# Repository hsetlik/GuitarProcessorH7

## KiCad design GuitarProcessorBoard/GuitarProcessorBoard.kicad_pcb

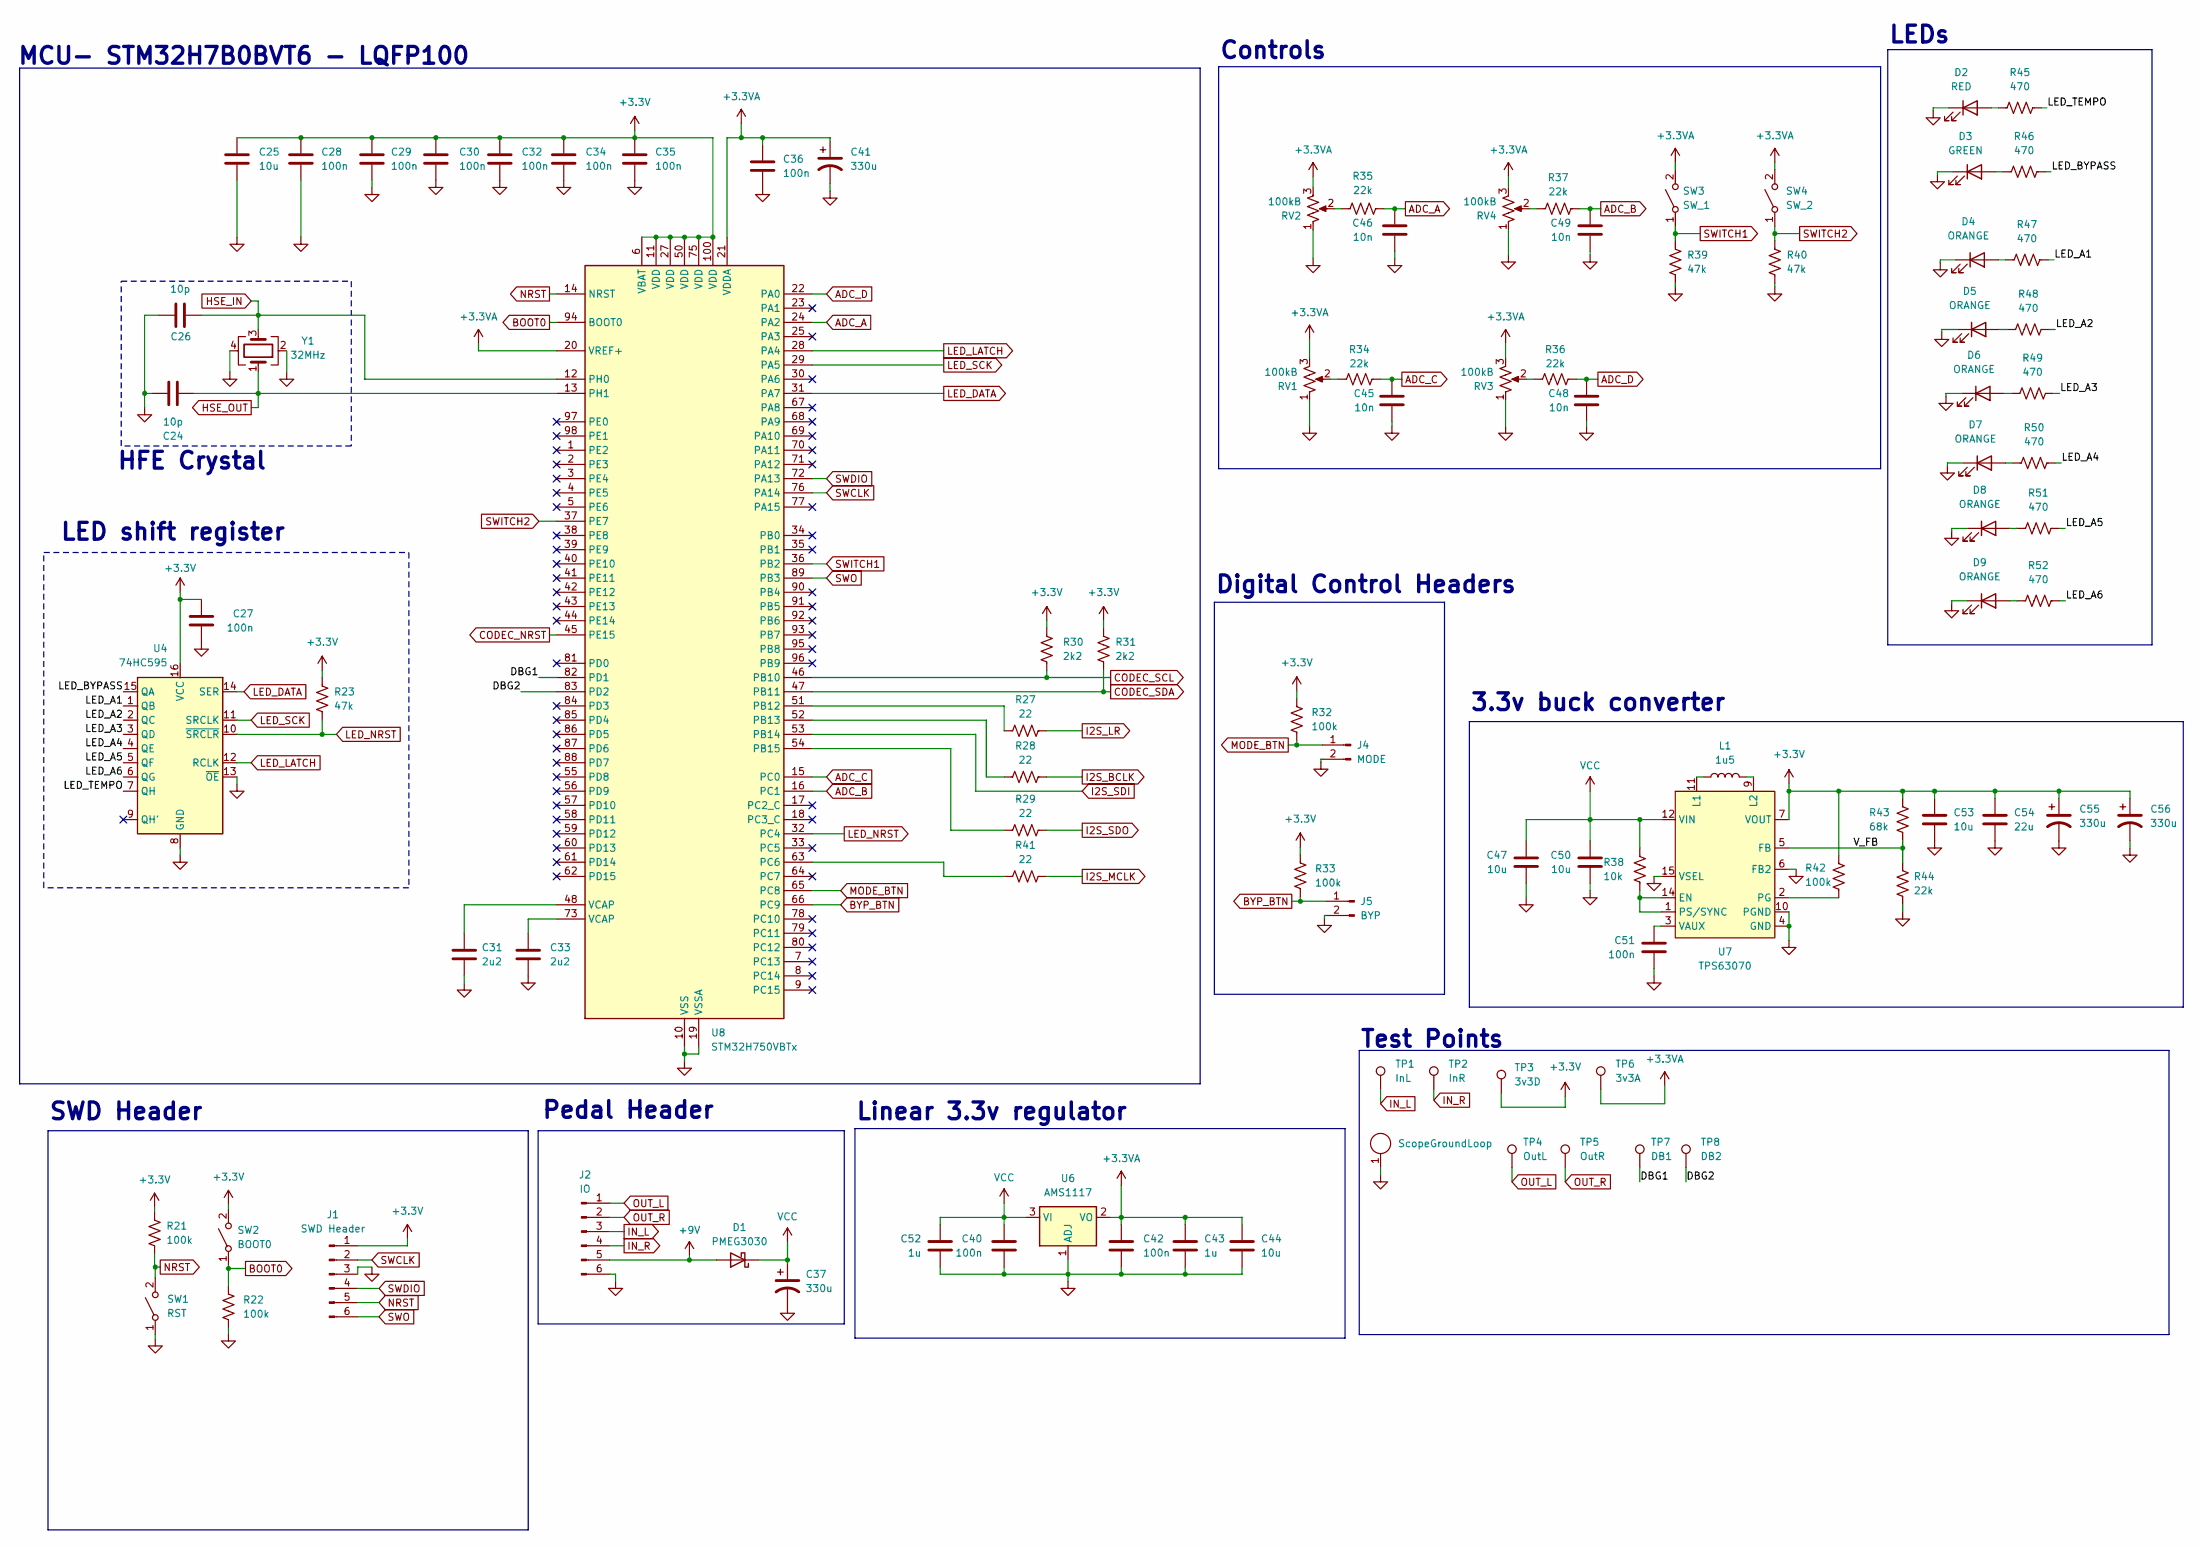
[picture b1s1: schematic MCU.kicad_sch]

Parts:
C24, C26: 10p; C_0805_2012Metric
C25, C44, C47, C50, C53: 10u; C_0805_2012Metric
C27, C28, C29, C30, C32, C34, C35, C36, C40, C42, C51: 100n; C_0805_2012Metric
C31, C33: 2u2; C_0805_2012Metric
C37, C41, C55, C56: 330u; CP_Radial_D5.0mm_P2.50mm
C43, C52: 1u; C_0805_2012Metric
C45, C46, C48, C49: 10n; C_0805_2012Metric
C54: 22u; C_0805_2012Metric
D1: PMEG3030; D_SOD-123
D2: RED; LED_D3.0mm
D3: GREEN; LED_D3.0mm
D4, D5, D6, D7, D8, D9: ORANGE; LED_D3.0mm
J1: SWD Header; PinHeader_1x06_P2.54mm_Vertical
J2: IO; PinHeader_1x06_P2.54mm_Vertical
J3: ScopeGroundLoop; THT_GND_WIRE
J4: MODE; PinHeader_1x02_P2.54mm_Vertical
J5: BYP; PinHeader_1x02_P2.54mm_Vertical
L1: 1u5; L_Coilcraft_XAL4020-XXX
R21, R22, R32, R33, R42: 100k; R_0805_2012Metric
R23, R39, R40: 47k; R_0805_2012Metric
R27, R28, R29, R41: 22; R_0805_2012Metric
R30, R31: 2k2; R_0805_2012Metric
R34, R35, R36, R37, R44: 22k; R_0805_2012Metric
R38: 10k; R_0805_2012Metric
R43: 68k; R_0805_2012Metric
R45, R46, R47, R48, R49, R50, R51, R52: 470; R_0805_2012Metric
RV1, RV2, RV3, RV4: 100kB; Potentiometer_Alpha_RD901F-40-00D_Single_Vertical_CircularH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
SW1: RST; SW_SPST_B3U-1000P
SW2: BOOT0; SW_SPST_B3U-1000P
SW3: SW_1; SW_TH_Tactile_Omron_B3F-102x
SW4: SW_2; SW_TH_Tactile_Omron_B3F-102x
TP1: InL; TestPoint_THTPad_D2.0mm_Drill1.0mm_VAL
TP2: InR; TestPoint_THTPad_D2.0mm_Drill1.0mm_VAL
TP3: 3v3D; TestPoint_THTPad_D2.0mm_Drill1.0mm_VAL
TP4: OutL; TestPoint_THTPad_D2.0mm_Drill1.0mm_VAL
TP5: OutR; TestPoint_THTPad_D2.0mm_Drill1.0mm_VAL
TP6: 3v3A; TestPoint_THTPad_D2.0mm_Drill1.0mm_VAL
TP7: DB1; TestPoint_THTPad_D2.0mm_Drill1.0mm_VAL
TP8: DB2; TestPoint_THTPad_D2.0mm_Drill1.0mm_VAL
U4: 74HC595; SOIC-16_3.9x9.9mm_P1.27mm
U6: AMS1117; SOT-223-3_TabPin2
U7: TPS63070; Converter_DCDC_TXN_QFN15
U8: STM32H750VBTx; LQFP-100_14x14mm_P0.5mm
Y1: 32MHz; Crystal_SMD_EuroQuartz_MT-4Pin_3.2x2.5mm

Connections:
+3.3V: C25.1, C27.1, C28.1, C29.1, C30.1, C32.1, C34.1, C35.1, C53.1, C54.1, C55.1, C56.1, J1.1, R21.1, R23.1, R30.1, R31.1, R32.1, R33.1, R42.1, R43.1, SW2.2 (B), TP3.1 (1_1), U4.16 (VCC), U7.7 (VOUT), U7.8 (VOUT), U8.6 (VBAT), U8.11 (VDD), U8.27 (VDD), U8.50 (VDD), U8.75 (VDD), U8.100 (VDD)
+3.3VA: C36.1, C41.1, C42.2, C43.1, C44.1, RV1.3, RV2.3, RV3.3, RV4.3, SW3.2 (B), SW4.2 (B), TP6.1 (1_1), U6.2 (VO), U8.20 (VREF+), U8.21 (VDDA); also elsewhere on the board
+9V: D1.2 (A), J2.5
/MCU/DBG1: TP7.1 (1_1), U8.82 (PD1)
/MCU/DBG2: TP8.1 (1_1), U8.83 (PD2)
/MCU/LED_A1: R47.2, U4.1 (QB)
/MCU/LED_A2: R48.2, U4.2 (QC)
/MCU/LED_A3: R49.2, U4.3 (QD)
/MCU/LED_A4: R50.2, U4.4 (QE)
/MCU/LED_A5: R51.2, U4.5 (QF)
/MCU/LED_A6: R52.2, U4.6 (QG)
/MCU/LED_BYPASS: R46.2, U4.15 (QA)
/MCU/LED_TEMPO: R45.2, U4.7 (QH)
/MCU/V_FB: R43.2, R44.1, U7.5 (FB)
ADC_A: C46.1, R35.2, U8.24 (PA2)
ADC_B: C49.1, R37.2, U8.16 (PC1)
ADC_C: C45.1, R34.2, U8.15 (PC0)
ADC_D: C48.1, R36.2, U8.22 (PA0)
BOOT0: R22.1, SW2.1 (A), U8.94 (BOOT0)
BYP_BTN: J5.1, R33.2, U8.66 (PC9)
CODEC_NRST: U8.45 (PE15); also elsewhere on the board
CODEC_SCL: R30.2, U8.46 (PB10); also elsewhere on the board
CODEC_SDA: R31.2, U8.47 (PB11); also elsewhere on the board
GND: C24.1, C25.2, C26.1, C27.2, C28.2, C29.2, C30.2, C31.2, C32.2, C33.2, C34.2, C35.2, C36.2, C37.2, C40.1, C41.2, C42.1, C43.2, C44.2, C45.2, C46.2, C47.2, C48.2, C49.2, C50.2, C51.2, C52.2, C53.2, C54.2, C55.2, C56.2, D2.1 (K), D3.1 (K), D4.1 (K), D5.1 (K), D6.1 (K), D7.1 (K), D8.1 (K), D9.1 (K), J1.3, J2.6, J3.1, J4.2, J5.2, R22.2, R39.2, R40.2, R44.2, RV1.1, RV2.1, RV3.1, RV4.1, SW1.1 (A), U4.8 (GND), U4.13 (~OE), U6.1 (ADJ), U7.4 (GND), U7.6 (FB2), U7.10 (PGND), U7.15 (VSEL), U8.10 (VSS), U8.19 (VSSA), U8.26 (VSS), U8.49 (VSS), U8.74 (VSS), U8.99 (VSS), Y1.2, Y1.4; also elsewhere on the board
HSE_IN: C26.2, U8.12 (PH0), Y1.3
HSE_OUT: C24.2, U8.13 (PH1), Y1.1
I2S_BCLK: R28.2; also elsewhere on the board
I2S_LR: R27.2; also elsewhere on the board
I2S_MCLK: R41.2; also elsewhere on the board
I2S_SDI: U8.53 (PB14); also elsewhere on the board
I2S_SDO: R29.2; also elsewhere on the board
IN_L: J2.3, TP1.1 (1_1); also elsewhere on the board
IN_R: J2.4, TP2.1 (1_1); also elsewhere on the board
LED_DATA: U4.14 (SER), U8.31 (PA7)
LED_LATCH: U4.12 (RCLK), U8.28 (PA4)
LED_NRST: R23.2, U4.10 (~SRCLR), U8.32 (PC4)
LED_SCK: U4.11 (SRCLK), U8.29 (PA5)
MODE_BTN: J4.1, R32.2, U8.65 (PC8)
NRST: J1.5, R21.2, SW1.2 (B), U8.14 (NRST)
unnamed: C31.1, U8.48 (VCAP)
unnamed: C33.1, U8.73 (VCAP)
unnamed: D2.2 (A), R45.1
unnamed: D3.2 (A), R46.1
unnamed: D4.2 (A), R47.1
unnamed: D5.2 (A), R48.1
unnamed: D6.2 (A), R49.1
unnamed: D7.2 (A), R50.1
unnamed: D8.2 (A), R51.1
unnamed: D9.2 (A), R52.1
unnamed: R34.1, RV1.2
unnamed: R35.1, RV2.2
unnamed: R36.1, RV3.2
unnamed: R37.1, RV4.2
unnamed: R38.2, U7.1 (PS/SYNC), U7.14 (EN)
unnamed: L1.1, U7.11 (L1)
unnamed: L1.2, U7.9 (L2)
unnamed: R42.2, U7.2 (PG)
unnamed: C51.1, U7.3 (VAUX)
unnamed: R27.1, U8.51 (PB12)
unnamed: R28.1, U8.52 (PB13)
unnamed: R29.1, U8.54 (PB15)
unnamed: R41.1, U8.63 (PC6)
OUT_L: J2.1, TP4.1 (1_1); also elsewhere on the board
OUT_R: J2.2, TP5.1 (1_1); also elsewhere on the board
SWCLK: J1.2, U8.76 (PA14)
SWDIO: J1.4, U8.72 (PA13)
SWITCH1: R39.1, SW3.1 (A), U8.36 (PB2)
SWITCH2: R40.1, SW4.1 (A), U8.37 (PE7)
SWO: J1.6, U8.89 (PB3)
VCC: C37.1, C40.2, C47.1, C50.1, C52.1, D1.1 (K), R38.1, U6.3 (VI), U7.12 (VIN), U7.13 (VIN); also elsewhere on the board

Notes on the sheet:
Pedal Header
3.3v buck converter
Linear 3.3v regulator
LED shift register
Test Points
HFE Crystal
LEDs
MCU- STM32H7B0BVT6 - LQFP100
SWD Header
Controls
Digital Control Headers

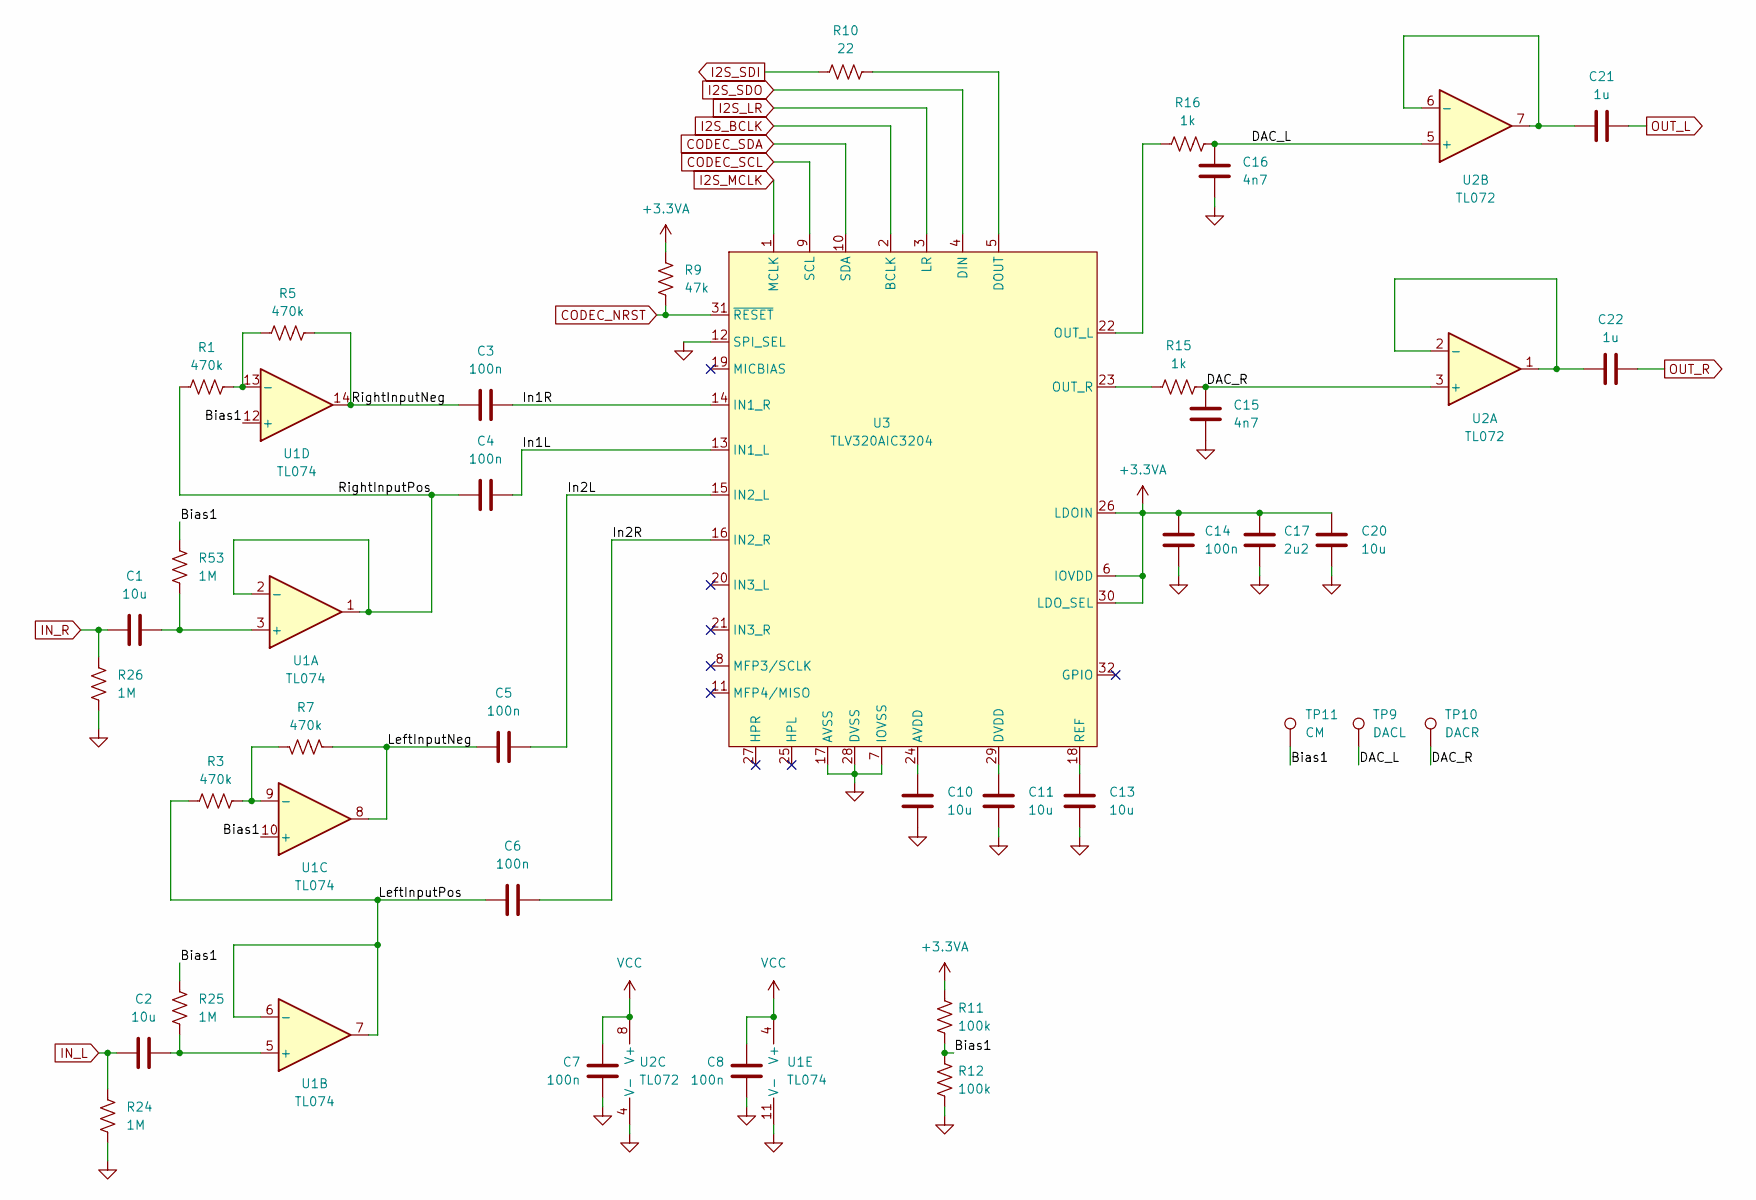
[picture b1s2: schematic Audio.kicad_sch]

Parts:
C1, C2, C10, C11, C13, C20: 10u; C_0805_2012Metric
C3, C4, C5, C6, C7, C8, C14: 100n; C_0805_2012Metric
C15, C16: 4n7; C_0805_2012Metric
C17: 2u2; C_0805_2012Metric
C21, C22: 1u; C_0805_2012Metric
R1, R3, R5, R7: 470k; R_0805_2012Metric
R9: 47k; R_0805_2012Metric
R10: 22; R_0805_2012Metric
R11, R12: 100k; R_0805_2012Metric
R15, R16: 1k; R_0805_2012Metric
R24, R25, R26, R53: 1M; R_0805_2012Metric
TP9: DACL; TestPoint_THTPad_D2.0mm_Drill1.0mm_VAL
TP10: DACR; TestPoint_THTPad_D2.0mm_Drill1.0mm_VAL
TP11: CM; TestPoint_THTPad_D2.0mm_Drill1.0mm_VAL
U1: TL074; SOIC-14_3.9x8.7mm_P1.27mm
U2: TL072; SOIC-8_3.9x4.9mm_P1.27mm
U3: TLV320AIC3204; VQFN-32-1EP_5x5mm_P0.5mm_EP3.1x3.1mm

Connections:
+3.3VA: C14.1, C17.1, C20.1, R9.1, R11.1, U3.6 (IOVDD), U3.26 (LDOIN), U3.30 (LDO_SEL); also elsewhere on the board
/Audio/Bias1: R11.2, R12.1, R25.1, R53.1, TP11.1 (1_1), U1.10 (+), U1.12 (+)
/Audio/DAC_L: C16.1, R16.2, TP9.1 (1_1), U2.5 (+)
/Audio/DAC_R: C15.1, R15.2, TP10.1 (1_1), U2.3 (+)
/Audio/In1L: C4.2, U3.13 (IN1_L)
/Audio/In1R: C3.2, U3.14 (IN1_R)
/Audio/In2L: C5.2, U3.15 (IN2_L)
/Audio/In2R: C6.2, U3.16 (IN2_R)
/Audio/LeftInputNeg: C5.1, R7.1, U1.8
/Audio/LeftInputPos: C6.1, R3.1, U1.6 (-), U1.7
/Audio/RightInputNeg: C3.1, R5.2, U1.14
/Audio/RightInputPos: C4.1, R1.1, U1.1, U1.2 (-)
CODEC_NRST: R9.2, U3.31 (~RESET); also elsewhere on the board
CODEC_SCL: U3.9 (SCL); also elsewhere on the board
CODEC_SDA: U3.10 (SDA); also elsewhere on the board
GND: C7.2, C8.2, C10.2, C11.2, C13.2, C14.2, C15.2, C16.2, C17.2, C20.2, R12.2, R24.2, R26.2, U1.11 (V-), U2.4 (V-), U3.7 (IOVSS), U3.12 (SPI_SEL), U3.17 (AVSS), U3.28 (DVSS), U3.33 (TP); also elsewhere on the board
I2S_BCLK: U3.2 (BCLK); also elsewhere on the board
I2S_LR: U3.3 (LR); also elsewhere on the board
I2S_MCLK: U3.1 (MCLK); also elsewhere on the board
I2S_SDI: R10.1; also elsewhere on the board
I2S_SDO: U3.4 (DIN); also elsewhere on the board
IN_L: C2.1, R24.1; also elsewhere on the board
IN_R: C1.1, R26.1; also elsewhere on the board
unnamed: C1.2, R53.2, U1.3 (+)
unnamed: C2.2, R25.2, U1.5 (+)
unnamed: R3.2, R7.2, U1.9 (-)
unnamed: R1.2, R5.1, U1.13 (-)
unnamed: C22.1, U2.1, U2.2 (-)
unnamed: C21.1, U2.6 (-), U2.7
unnamed: C10.1, U3.24 (AVDD)
unnamed: R10.2, U3.5 (DOUT)
unnamed: C11.1, U3.29 (DVDD)
unnamed: R16.1, U3.22 (OUT_L)
unnamed: R15.1, U3.23 (OUT_R)
unnamed: C13.1, U3.18 (REF)
OUT_L: C21.2; also elsewhere on the board
OUT_R: C22.2; also elsewhere on the board
VCC: C7.1, C8.1, U1.4 (V+), U2.8 (V+); also elsewhere on the board

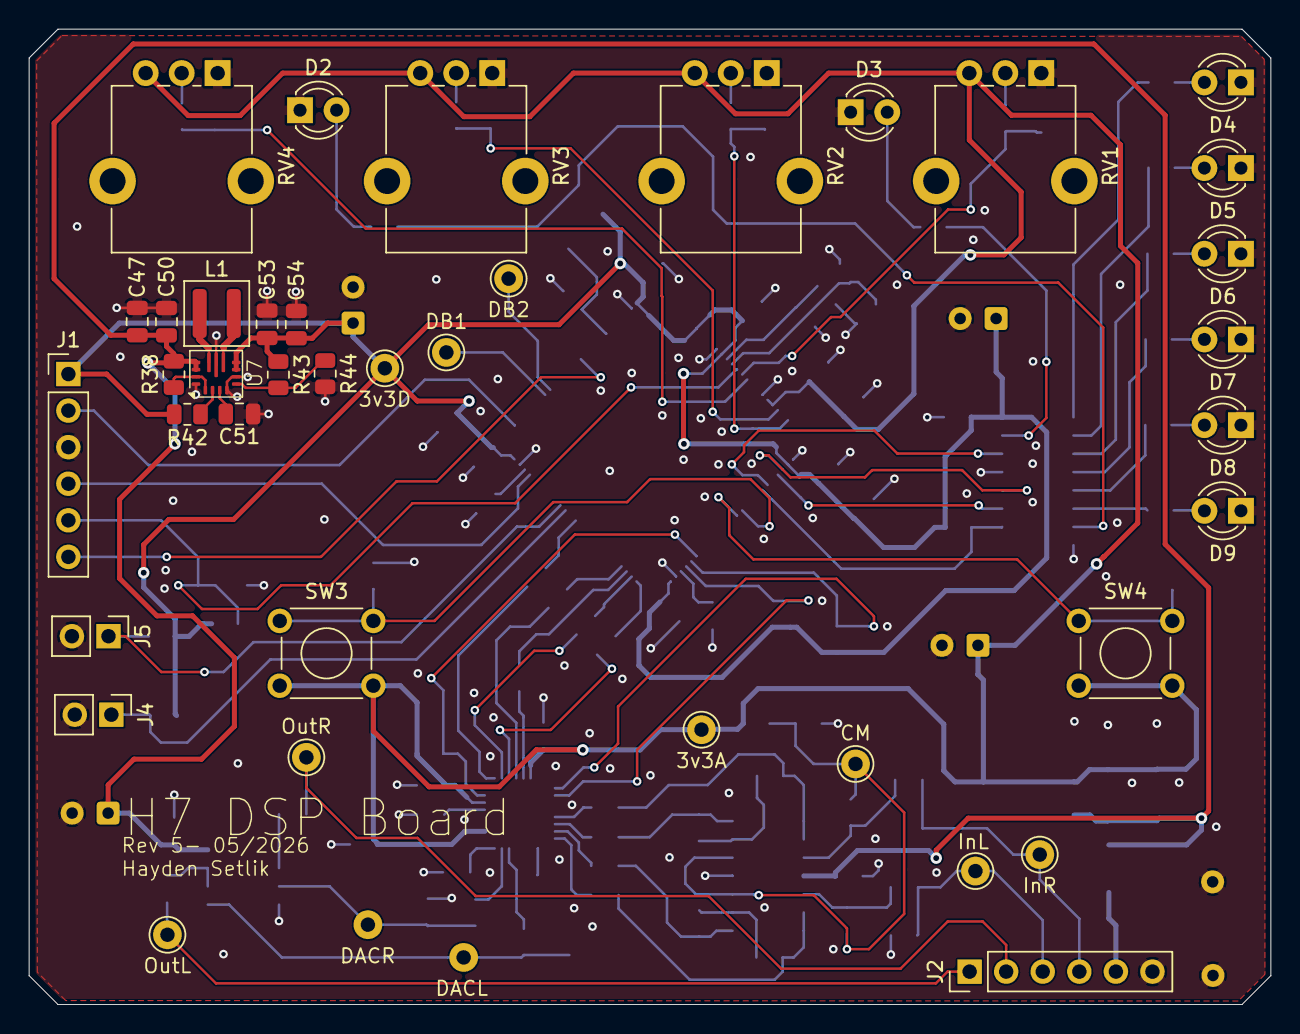
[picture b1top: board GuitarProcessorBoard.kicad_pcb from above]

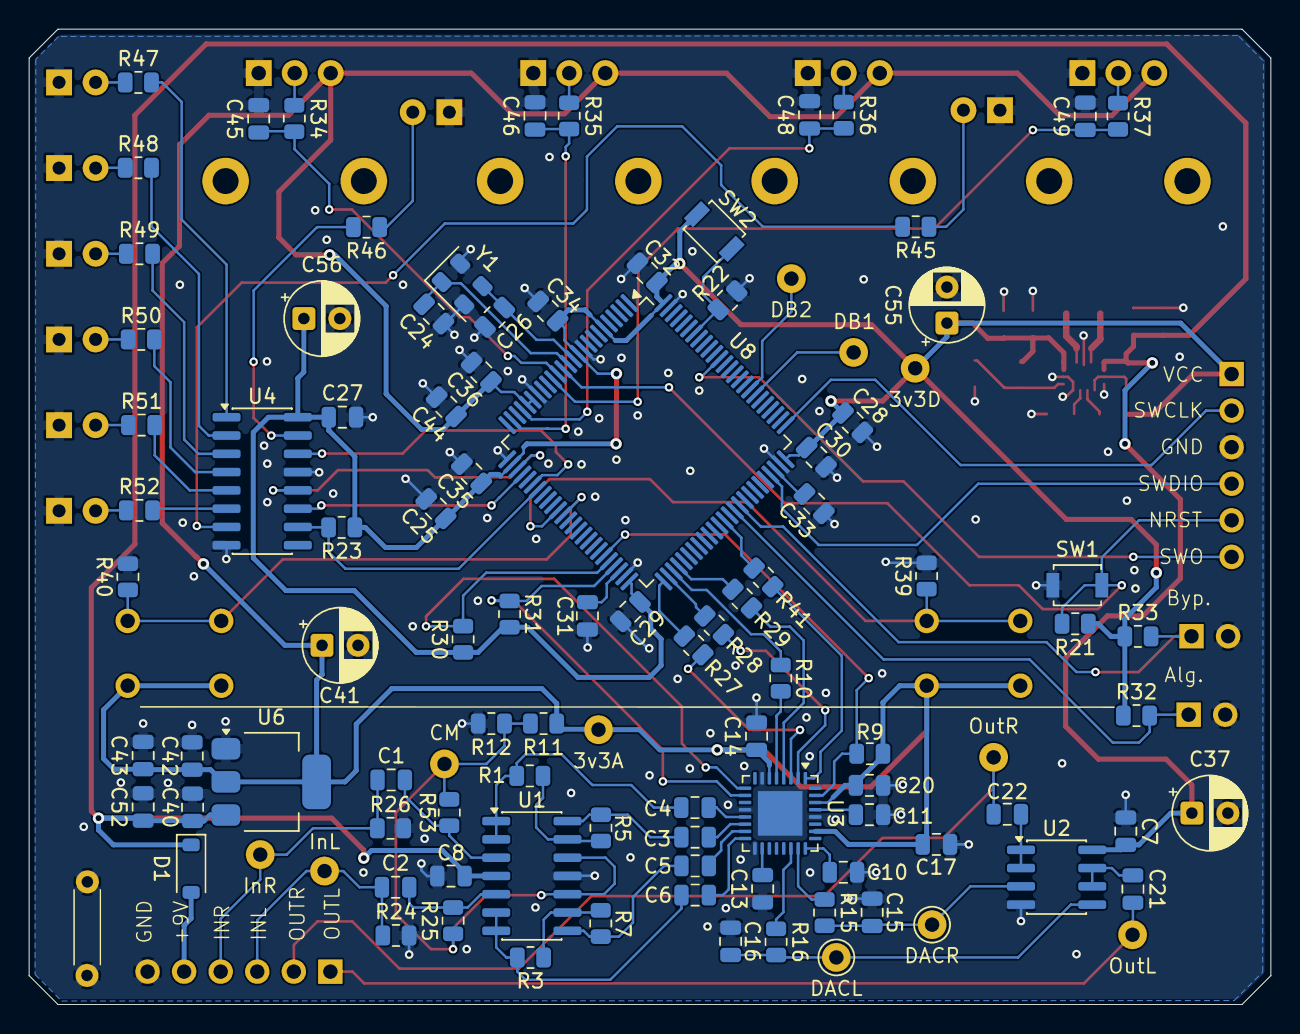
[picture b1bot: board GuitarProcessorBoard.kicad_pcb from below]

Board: 4 copper layers, 86.3 x 67.8 mm, 134 parts (96 on the bottom side), 93 nets.

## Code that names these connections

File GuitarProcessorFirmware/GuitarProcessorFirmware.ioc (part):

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Mcu.Name=STM32H750VBTx
Mcu.Package=LQFP100
Mcu.UserName=STM32H750VBTx
PA0.GPIOParameters=GPIO_Label
PA0.GPIO_Label=ADC_D
PA0.Mode=IN16-Single-Ended
PA0.Signal=ADC1_INP16
PA13\ (JTMS/SWDIO).Mode=Trace_Asynchronous_SW
PA13\ (JTMS/SWDIO).Signal=DEBUG_JTMS-SWDIO
PA14\ (JTCK/SWCLK).Mode=Trace_Asynchronous_SW
PA14\ (JTCK/SWCLK).Signal=DEBUG_JTCK-SWCLK
PA2.GPIOParameters=GPIO_Label
PA2.GPIO_Label=ADC_A
PA2.Signal=ADCx_INP14
PA4.GPIOParameters=GPIO_Label
PA4.GPIO_Label=LED_LATCH
PA4.Mode=NSS_Signal_Hard_Output
PA4.Signal=SPI1_NSS
PA5.GPIOParameters=GPIO_Label
PA5.GPIO_Label=LED_CLK
PA5.Mode=TX_Only_Simplex_Unidirect_Master
PA5.Signal=SPI1_SCK
PA7.GPIOParameters=GPIO_Label
PA7.GPIO_Label=LED_DATA
PA7.Mode=TX_Only_Simplex_Unidirect_Master
PA7.Signal=SPI1_MOSI
PB10.GPIOParameters=GPIO_Label
PB10.GPIO_Label=CODEC_SCL
PB10.Mode=I2C
PB10.Signal=I2C2_SCL
PB11.GPIOParameters=GPIO_Label
PB11.GPIO_Label=CODEC_SDA
PB11.Mode=I2C
PB11.Signal=I2C2_SDA
PB12.Mode=Full_Duplex_Master
PB12.Signal=I2S2_WS
PB13.Mode=Full_Duplex_Master
PB13.Signal=I2S2_CK
PB14.Mode=Full_Duplex_Master
PB14.Signal=I2S2_SDI
PB15.Mode=Full_Duplex_Master
PB15.Signal=I2S2_SDO
PB2.GPIOParameters=GPIO_Label
PB2.GPIO_Label=SW_1
PB2.Signal=GPIO_Input
PB3\ (JTDO/TRACESWO).Mode=Trace_Asynchronous_SW
PB3\ (JTDO/TRACESWO).Signal=DEBUG_JTDO-SWO
PC0.GPIOParameters=GPIO_Label
PC0.GPIO_Label=ADC_C
PC0.Signal=ADCx_INP10
PC1.GPIOParameters=GPIO_Label
PC1.GPIO_Label=ADC_B
PC1.Signal=ADCx_INP11
PC4.GPIOParameters=GPIO_Label
PC4.GPIO_Label=LED_NRST
PC4.Signal=GPIO_Output
PC6.Mode=Master_Clock_Activated
PC6.Signal=I2S2_MCK
PC8.GPIOParameters=GPIO_Label
PC8.GPIO_Label=MODE
PC8.Signal=GPIO_Input
PC9.GPIOParameters=GPIO_Label
PC9.GPIO_Label=BYP
PC9.Signal=GPIO_Input
PD1.GPIOParameters=GPIO_Label
PD1.GPIO_Label=DBG1
PD1.Signal=GPIO_Output
PD2.GPIOParameters=GPIO_Label
PD2.GPIO_Label=DBG2
PD2.Signal=GPIO_Output
PE15.GPIOParameters=PinState,GPIO_Label
PE15.GPIO_Label=CODEC_NRST
PE15.PinState=GPIO_PIN_SET
PE15.Signal=GPIO_Output
PE7.GPIOParameters=GPIO_Label
PE7.GPIO_Label=SW_2
PE7.Signal=GPIO_Input
PH0-OSC_IN\ (PH0).Mode=HSE-External-Oscillator
PH0-OSC_IN\ (PH0).Signal=RCC_OSC_IN
PH1-OSC_OUT\ (PH1).Mode=HSE-External-Oscillator
PH1-OSC_OUT\ (PH1).Signal=RCC_OSC_OUT
RCC.HSE_VALUE=32000000
RCC.SYSCLKFreq_VALUE=480000000
RCC.SYSCLKSource=RCC_SYSCLKSOURCE_PLLCLK
board=custom

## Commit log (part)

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2025-01-13 preliminary pinout
2025-01-13 audio codec schematic
2025-01-13 I2S boilerplate
2025-01-21 basic MCU pinout, IO headers
2025-01-21 control wiring
2025-01-21 switched to shift register LEDs
2025-01-21 added analog wet/dry control
2025-01-21 control/ enclosure layout
2025-01-21 starting layout
2025-01-22 removed encoder and back btn
2025-01-22 first layout
2025-01-23 routing rd one
2025-01-24 routed & DRC passing
2025-01-24 silkscreen, stitching vias
2025-01-24 more test points, trace clean up
2025-01-24 rev1 gerber
2025-01-24 added BOM
2025-01-24 enclosure SVG stuff
2025-01-27 processing callback set up
2025-01-27 processor state stuff
2025-01-29 register access for TLV320AIC codec
2025-01-29 codec register map defines
2025-01-29 more driver stuff
2025-02-02 codec initialization HAL
2025-02-04 set up DMA for control knobs
2025-02-04 FxAlgorithm scheme, led shift register driver
2025-02-04 added CMSIS v4 library
2025-02-04 convolution FIR filter implementation
2025-02-04 RingBuffer and peak detector
2025-02-13 IIR filter general form
2025-02-14 peak detector implementation
2025-02-14 delay line implementation
2025-02-14 adding DSP math
2025-02-14 IIR Biquad implementation
2025-02-14 pole/zero layout stuff
2025-02-14 Biquad cascade
2025-02-14 cascade, pole filter base
2025-02-14 pole filter s/z transforms
2025-02-14 butterworth analog prototypes
2025-02-15 high pass and low pass Butterworth classes
2025-02-15 Butterworth shelf filters
2025-02-15 added display driver
2025-02-16 new Delay line stuff
2025-02-17 dattorro reverb implementation
2025-02-17 new envelope follower
2025-02-18 fixed IIR bug
2025-02-18 Added DMA mode to display driver
2025-02-18 Octave shifting stuff
2025-02-19 stuff for cmsis FFT
2025-02-19 FFT effect skeleton
2025-02-19 basic sine wave LFO
2025-02-19 some wacky FFT phasing ideas
2025-02-20 fft phasing modes
2025-02-20 better bin randomizing algo
2025-02-20 phaser knob controls
2025-02-20 switched to 48kHz audio
2025-02-20 RMS meter
2025-07-09 without hardware RNG
2025-07-10 codec input side setup
2025-07-10 hardware I2S troubleshooting
2025-07-11 codec I2C bus working in hardware
2025-07-12 getting ADC data on 32 bit frames
2025-07-12 DAC registers set up
2025-07-12 single-ended output working
2025-07-13 differential output stage
2025-07-13 schematic changes
2025-07-13 differential output sim
2025-07-13 routing start
2025-07-13 DRC passing
2025-07-14 trying basic reverb
2025-07-16 single-ended output double buffer working
2025-07-17 alg. switch handling
2025-07-17 control knob ADC working
2025-07-17 moved ADC callback to timer 4
2025-07-17 bypass switching works
2025-07-24 display stuff
2025-07-24 more decoupling caps, return vias
2025-07-24 timer interrupt for screen redraws
2025-07-24 moved display work out of ISR
2025-07-28 display interrupt fixed
2025-07-28 RMS and bias meters working
2025-07-28 Display DMA mode works
2025-07-28 moved per-page command messages to DMA as well
2025-07-28 bumped I2C clock to 220khZ, 18fps working
2025-07-31 IRQ scheduling changes
2026-01-12 split PSU schematic, DRC passing
2026-01-12 new split power branch
2026-01-13 stitching vias, prettier layout
2026-01-18 rev2 sent to fab
2026-01-25 updated to kicad 9, new BOM file
2026-02-01 migrated to new cube MX version, flashing on new board works
2026-02-03 switched off display stuff for now
2026-04-02 basic cpp stuff in cmake/vscode
2026-04-02 audio codec driver set up
2026-04-04 code flashing woooo
2026-04-04 wrestling w I2S and codec setup
2026-04-05 tracking linker script
2026-04-06 audio DMA finally working wooot
2026-04-06 switched back to 32 bit word size
2026-04-06 boilerplate chunk processing
2026-04-06 undid memory changes
2026-04-06 fixed linker script, switched to 12 bit for knob readings
2026-04-07 back 2 32 bit word length
2026-04-08 defines for come control bytes
2026-04-09 Basic coded throughput working w/ 16 bit word length
2026-04-09 dialing in 16 bit codec setup
2026-04-11 differential outpur on right DAC working
2026-04-11 tweaked resistor for input/output gain
2026-04-12 PedalState, button reading and LEDs
2026-04-12 sample to float conversion set up
2026-04-12 24 bit words working, sample to float conv working
2026-04-12 fixed jumping to alg2 on startup
2026-04-12 set up cpp support in cmakelists
2026-04-12 set up FxAlgorithm/FxProcessor scheme
2026-04-13 delay line
2026-04-13 32 bit depth. why da hell not.
2026-04-13 basic Dattorro implementation
2026-04-13 added AXISRAMPool, reverb is still too slow
2026-04-13 bumped clock t0 216mhz
2026-04-15 Basic Schroeder implementation
2026-04-15 controls on schroeder verb
2026-04-18 updated schematic, re-annotated
2026-04-19 new layout
2026-04-19 prelim. routing, DRC passing
2026-04-20 minor tweaks
2026-04-20 new layout, pinout switcharoo
2026-04-20 prelim routing, DRC passing
2026-04-21 stitching vias, silkscreen, spacing
2026-04-21 rev3 sent to fab
2026-04-21 codec initialization for stereo setup
2026-04-22 stereo processing callbacks in FxAlgorithm/Processor scheme
2026-04-27 comb and allpass filters for Freeverb impl
2026-05-01 board too tall ughhhhh
2026-05-01 shorter board
2026-05-01 rev4 sent to fab
2026-05-02 new Denormal handling
2026-05-02 handling for 4th knob and switches
2026-05-02 stereo processing callback in main, debug pin access
2026-05-02 fleshed out freeverb implementation
2026-05-03 added NormRange
2026-05-03 controls and ranges for freeverb
2026-05-10 fixed drill pattern
2026-05-12 rev4 code flashing
2026-05-16 address finding business
2026-05-16 stereo throughput working
2026-05-17 bumped to 280MhZ
2026-05-17 switched to H750VBT6
2026-05-17 switched to new linker script
2026-05-17 updated schem for new MCU part num
2026-05-21 Code flashing w/ H750 soldered wooo
2026-05-21 fixed weirdness w adc conversions, schroeder and freeverb working
2026-05-21 fixes for Dattorro alg
2026-05-22 humting down mysterious DC input bias
2026-05-23 input/output opamp stages changed
2026-05-23 basic routing, DRC passes
2026-05-23 stitching vias, silkscreen, corner bevels
2026-05-24 rev5 sent to fab
2026-05-27 tracked BOM
2026-05-27 generic button debouncing
2026-06-04 rev5 board flashing, mode buttons working
2026-06-06 Dattorro verb running fast enough woo
2026-06-09 knob controls and wet/dry mix for Dattorro
